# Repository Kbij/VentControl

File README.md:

# VentControl

Firmware for a custom made RP-2040 board with relays. Used for Ventilation control.

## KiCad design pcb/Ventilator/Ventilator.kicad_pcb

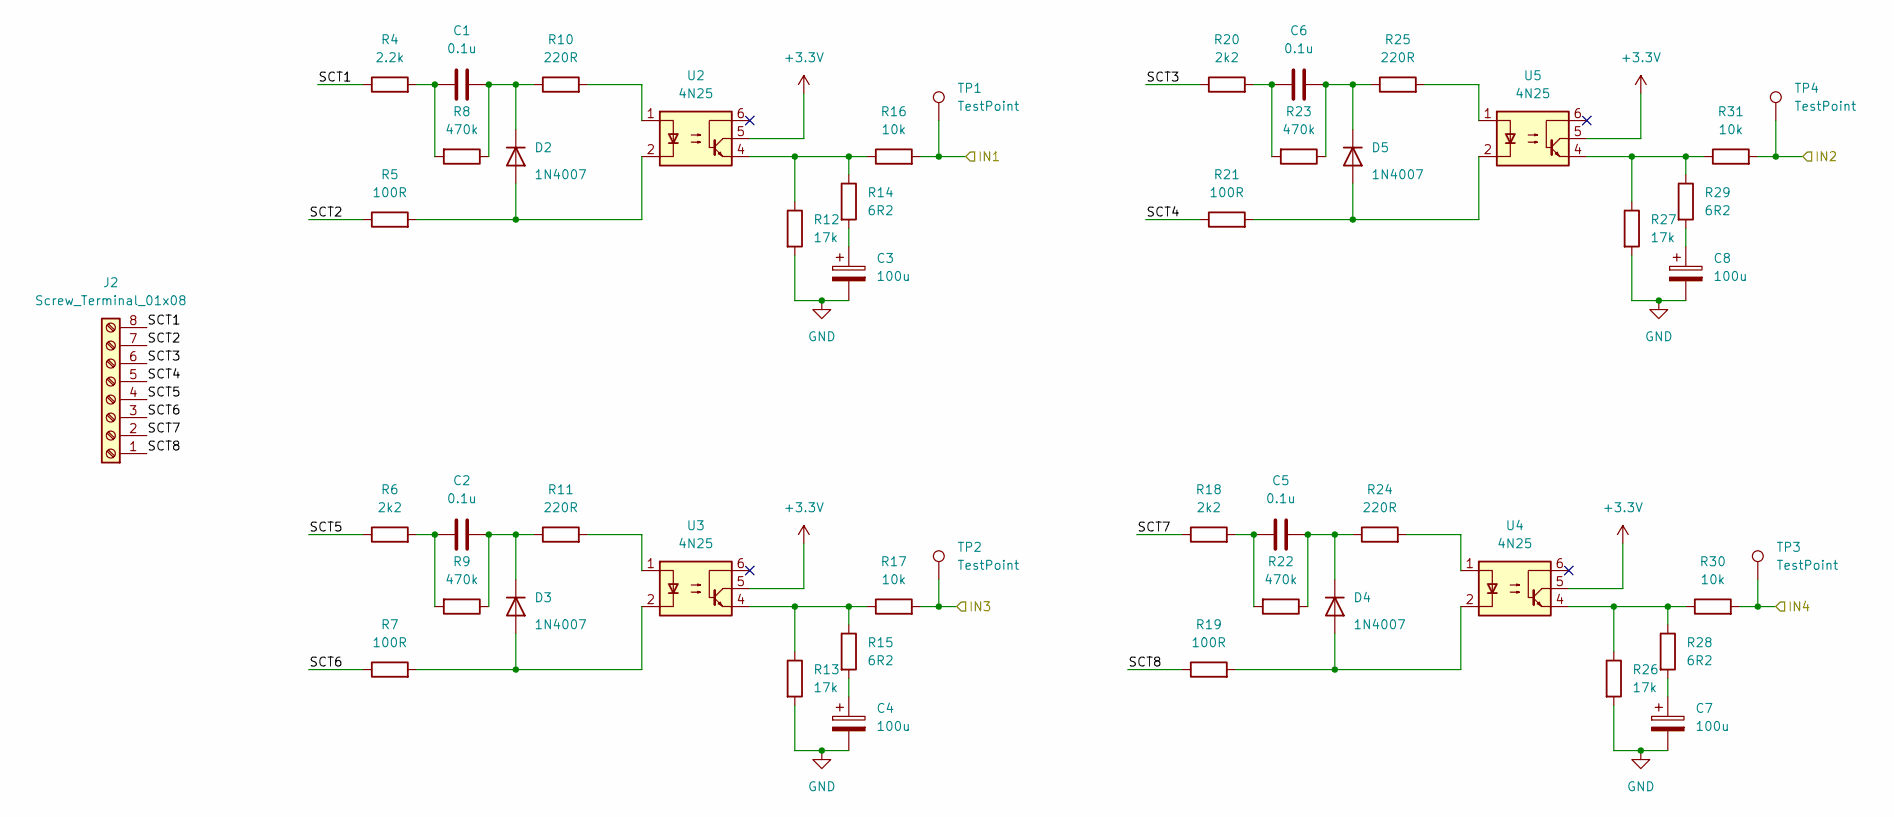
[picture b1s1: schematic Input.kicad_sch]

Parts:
C1, C2, C5, C6: 0.1u; C_Rect_L18.0mm_W5.0mm_P15.00mm_FKS3_FKP3
C3, C4, C7, C8: 100u; C_1206_3216Metric_Pad1.33x1.80mm_HandSolder
D2, D3, D4, D5: 1N4007; D_DO-41_SOD81_P10.16mm_Horizontal
J2: Screw_Terminal_01x08; TerminalBlock_Phoenix_MKDS-1,5-8_1x08_P5.00mm_Horizontal
R4: 2.2k; R_2512_6332Metric
R5, R7, R19, R21: 100R; R_0805_2012Metric_Pad1.20x1.40mm_HandSolder
R6, R18, R20: 2k2; R_2512_6332Metric
R8, R9, R22, R23: 470k; R_2512_6332Metric
R10, R11, R24, R25: 220R; R_0805_2012Metric_Pad1.20x1.40mm_HandSolder
R12, R13, R26, R27: 17k; R_0805_2012Metric_Pad1.20x1.40mm_HandSolder
R14, R15, R28, R29: 6R2; R_0805_2012Metric_Pad1.20x1.40mm_HandSolder
R16, R17, R30, R31: 10k; R_0805_2012Metric_Pad1.20x1.40mm_HandSolder
TP1, TP2, TP3, TP4: TestPoint; TestPoint_Bridge_Pitch2.54mm_Drill1.0mm
U2, U3, U4, U5: 4N25; DIP-6_W7.62mm

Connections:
+3.3V: U2.5, U3.5, U4.5, U5.5; also elsewhere on the board
/CPU/IN1: R16.2, TP1.1; also elsewhere on the board
/CPU/IN2: R31.2, TP4.1; also elsewhere on the board
/CPU/IN3: R17.2, TP2.1; also elsewhere on the board
/CPU/IN4: R30.2, TP3.1; also elsewhere on the board
/Input/SCT1: J2.8, R4.1; also elsewhere on the board
/Input/SCT2: J2.7, R5.1; also elsewhere on the board
/Input/SCT3: J2.6, R20.1; also elsewhere on the board
/Input/SCT4: J2.5, R21.1; also elsewhere on the board
/Input/SCT5: J2.4, R6.1; also elsewhere on the board
/Input/SCT6: J2.3, R7.1; also elsewhere on the board
/Input/SCT7: J2.2, R18.1; also elsewhere on the board
/Input/SCT8: J2.1, R19.1; also elsewhere on the board
GND: C3.2, C4.2, C7.2, C8.2, R12.2, R13.2, R26.2, R27.2; also elsewhere on the board
unnamed 30: C1.1, D2.1 (K), R8.1, R10.1; also elsewhere on the board
unnamed 31: C1.2, R4.2, R8.2; also elsewhere on the board
unnamed: C2.1, D3.1 (K), R9.1, R11.1
unnamed: C2.2, R6.2, R9.2
unnamed: C3.1, R14.2
unnamed: C4.1, R15.2
unnamed: C5.1, D4.1 (K), R22.1, R24.1
unnamed: C5.2, R18.2, R22.2
unnamed: C6.1, D5.1 (K), R23.1, R25.1
unnamed: C6.2, R20.2, R23.2
unnamed: C7.1, R28.2
unnamed: C8.1, R29.2
unnamed: D2.2 (A), R5.2, U2.2
unnamed: D3.2 (A), R7.2, U3.2
unnamed: D4.2 (A), R19.2, U4.2
unnamed: D5.2 (A), R21.2, U5.2
unnamed: R10.2, U2.1
unnamed: R11.2, U3.1
unnamed: R12.1, R14.1, R16.1, U2.4
unnamed: R13.1, R15.1, R17.1, U3.4
unnamed: R24.2, U4.1
unnamed: R25.2, U5.1
unnamed: R26.1, R28.1, R30.1, U4.4
unnamed: R27.1, R29.1, R31.1, U5.4

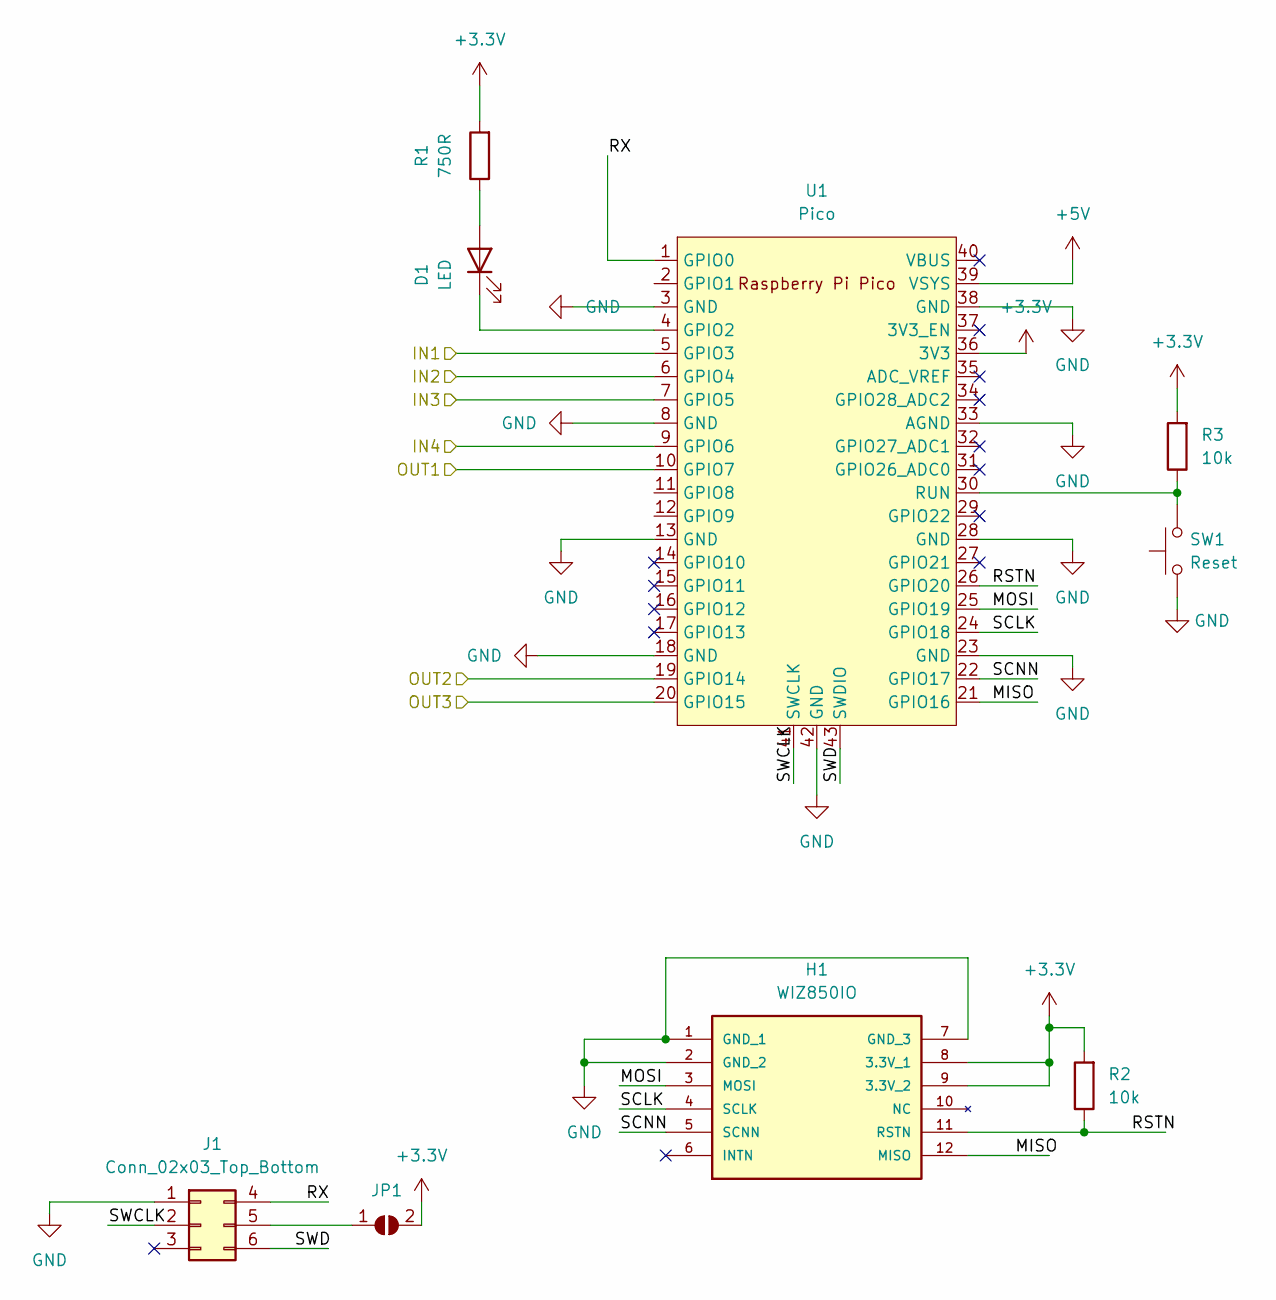
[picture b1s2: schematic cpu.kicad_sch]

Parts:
D1: LED; LED_D3.0mm
H1: WIZ850IO; MANUFACTURER_PART_NUMBER WIZ850IO
J1: Conn_02x03_Top_Bottom; PinHeader_2x03_P2.54mm_Vertical
JP1: SolderJumper_2_Open
R1: 750R; R_0805_2012Metric_Pad1.20x1.40mm_HandSolder
R2, R3: 10k; R_0805_2012Metric
SW1: Reset; SW_SPST_EVPBF
U1: Pico; RPi_Pico_SMD_TH

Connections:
+3.3V: H1.8 (3.3V_1), H1.9 (3.3V_2), JP1.2 (B), R1.2, R2.2, R3.2, U1.36 (3V3); also elsewhere on the board
+5V: U1.39 (VSYS); also elsewhere on the board
/CPU/IN1: U1.5 (GPIO3); also elsewhere on the board
/CPU/IN2: U1.6 (GPIO4); also elsewhere on the board
/CPU/IN3: U1.7 (GPIO5); also elsewhere on the board
/CPU/IN4: U1.9 (GPIO6); also elsewhere on the board
/CPU/MISO: H1.12 (MISO), U1.21 (GPIO16)
/CPU/MOSI: H1.3 (MOSI), U1.25 (GPIO19)
/CPU/OUT1: U1.10 (GPIO7); also elsewhere on the board
/CPU/OUT2: U1.19 (GPIO14); also elsewhere on the board
/CPU/OUT3: U1.20 (GPIO15); also elsewhere on the board
/CPU/RSTN: H1.11 (RSTN), R2.1, U1.26 (GPIO20)
/CPU/RX: J1.4, U1.1 (GPIO0)
/CPU/SCLK: H1.4 (SCLK), U1.24 (GPIO18)
/CPU/SCNN: H1.5 (SCNN), U1.22 (GPIO17)
/CPU/SWCLK: J1.2, U1.41 (SWCLK)
/CPU/SWD: J1.6, U1.43 (SWDIO)
GND: H1.1 (GND_1), H1.2 (GND_2), H1.7 (GND_3), J1.1, SW1.1, U1.3 (GND), U1.8 (GND), U1.13 (GND), U1.18 (GND), U1.23 (GND), U1.28 (GND), U1.33 (AGND), U1.38 (GND), U1.42 (GND); also elsewhere on the board
unnamed: D1.1 (K), U1.4 (GPIO2)
unnamed: D1.2 (A), R1.1
unnamed: J1.5, JP1.1 (A)
unnamed: R3.1, SW1.2, U1.30 (RUN)

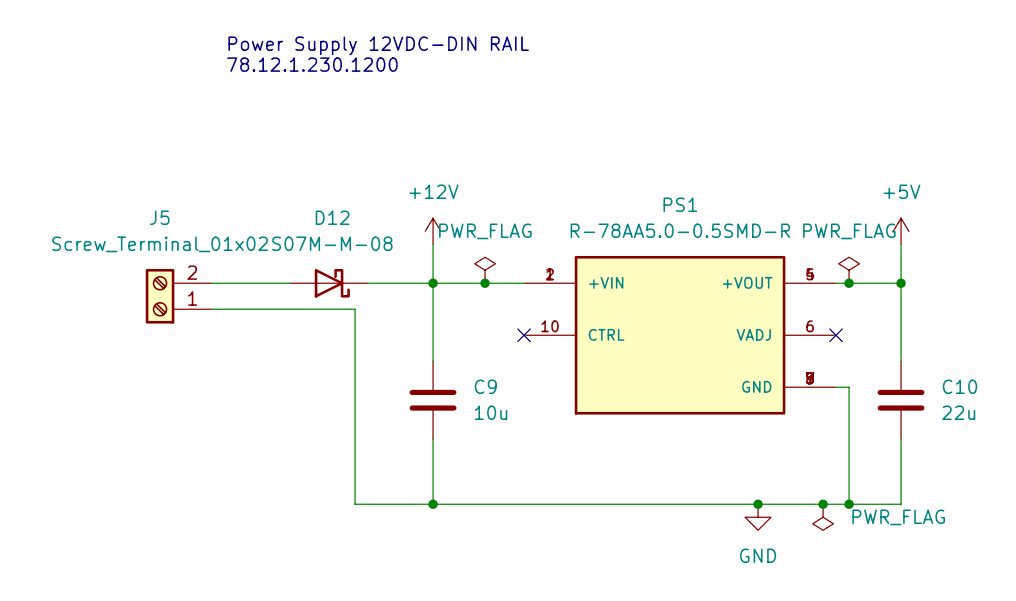
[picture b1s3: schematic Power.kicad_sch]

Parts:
C9: 10u; C_0805_2012Metric_Pad1.18x1.45mm_HandSolder
C10: 22u; C_0805_2012Metric_Pad1.18x1.45mm_HandSolder
D12: S07M-M-08; D_SMF
J5: Screw_Terminal_01x02; TerminalBlock_bornier-2_P5.08mm
PS1: R-78AA5.0-0.5SMD-R; CONV_R-78AA3.3-1.0SMD; PARTREV 5/2019

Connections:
+5V: C10.1, PS1.4 (+VOUT), PS1.5 (+VOUT); also elsewhere on the board
+12V: C9.1, D12.1 (K), PS1.1 (+VIN), PS1.2 (+VIN); also elsewhere on the board
GND: C9.2, C10.2, J5.1, PS1.3 (GND), PS1.7 (GND), PS1.8 (GND), PS1.9 (GND); also elsewhere on the board
unnamed: D12.2 (A), J5.2

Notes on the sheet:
Power Supply 12VDC-DIN RAIL 78.12.1.230.1200

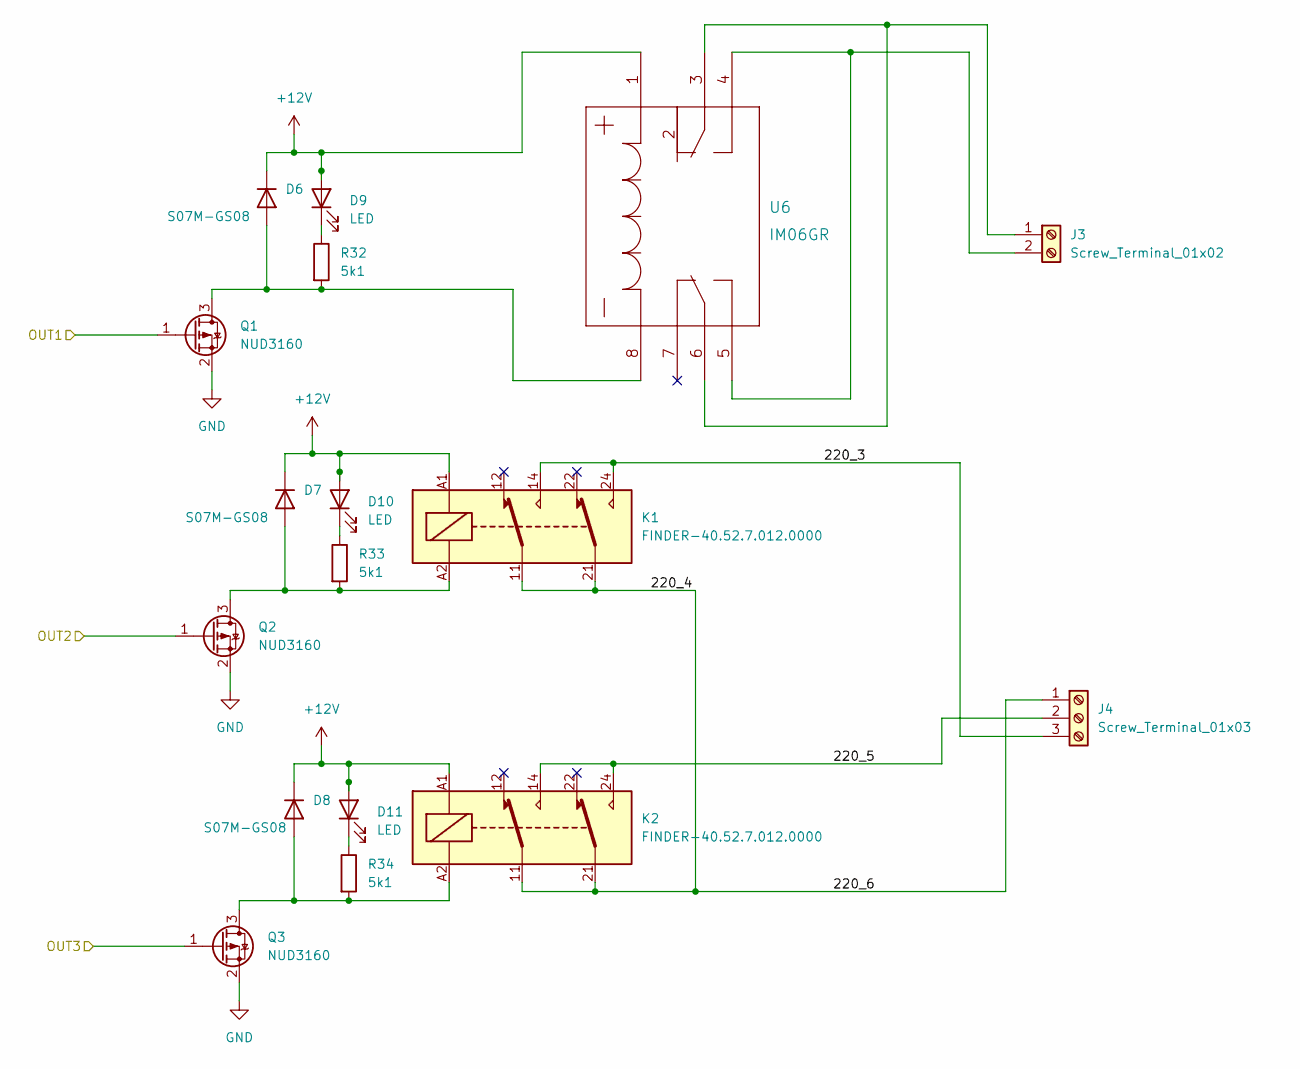
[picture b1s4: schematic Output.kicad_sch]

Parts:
D6, D7, D8: S07M-GS08; D_SMF
D9, D10, D11: LED; LED_D3.0mm
J3: Screw_Terminal_01x02; TerminalBlock_Phoenix_MKDS-1,5-2-5.08_1x02_P5.08mm_Horizont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
J4: Screw_Terminal_01x03; TerminalBlock_Phoenix_MKDS-1,5-3-5.08_1x03_P5.08mm_Horizont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
K1, K2: FINDER-40.52.7.012.0000; Relay_DPDT_Finder_40.52
Q1, Q2, Q3: NUD3160; SOT-23
R32, R33, R34: 5k1; R_0805_2012Metric_Pad1.20x1.40mm_HandSolder
U6: IM06GR

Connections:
+12V: D6.1 (K), D7.1 (K), D8.1 (K), D9.2 (A), D10.2 (A), D11.2 (A), K1.A1, K2.A1, U6.1; also elsewhere on the board
/CPU/OUT1: Q1.1 (G); also elsewhere on the board
/CPU/OUT2: Q2.1 (G); also elsewhere on the board
/CPU/OUT3: Q3.1 (G); also elsewhere on the board
/Output/220_3: J4.3, K1.14, K1.24
/Output/220_4: J4.1, K1.11, K1.21, K2.11, K2.21; also elsewhere on the board
/Output/220_5: J4.2, K2.14, K2.24; also elsewhere on the board
GND: Q1.2 (S), Q2.2 (S), Q3.2 (S); also elsewhere on the board
unnamed: D6.2 (A), Q1.3 (D), R32.2, U6.8
unnamed: D7.2 (A), K1.A2, Q2.3 (D), R33.2
unnamed 50: D8.2 (A), K2.A2, Q3.3 (D), R34.2; also elsewhere on the board
unnamed: D9.1 (K), R32.1
unnamed: D10.1 (K), R33.1
unnamed 53: D11.1 (K), R34.1; also elsewhere on the board
unnamed: J3.1, U6.3, U6.6
unnamed: J3.2, U6.4, U6.5

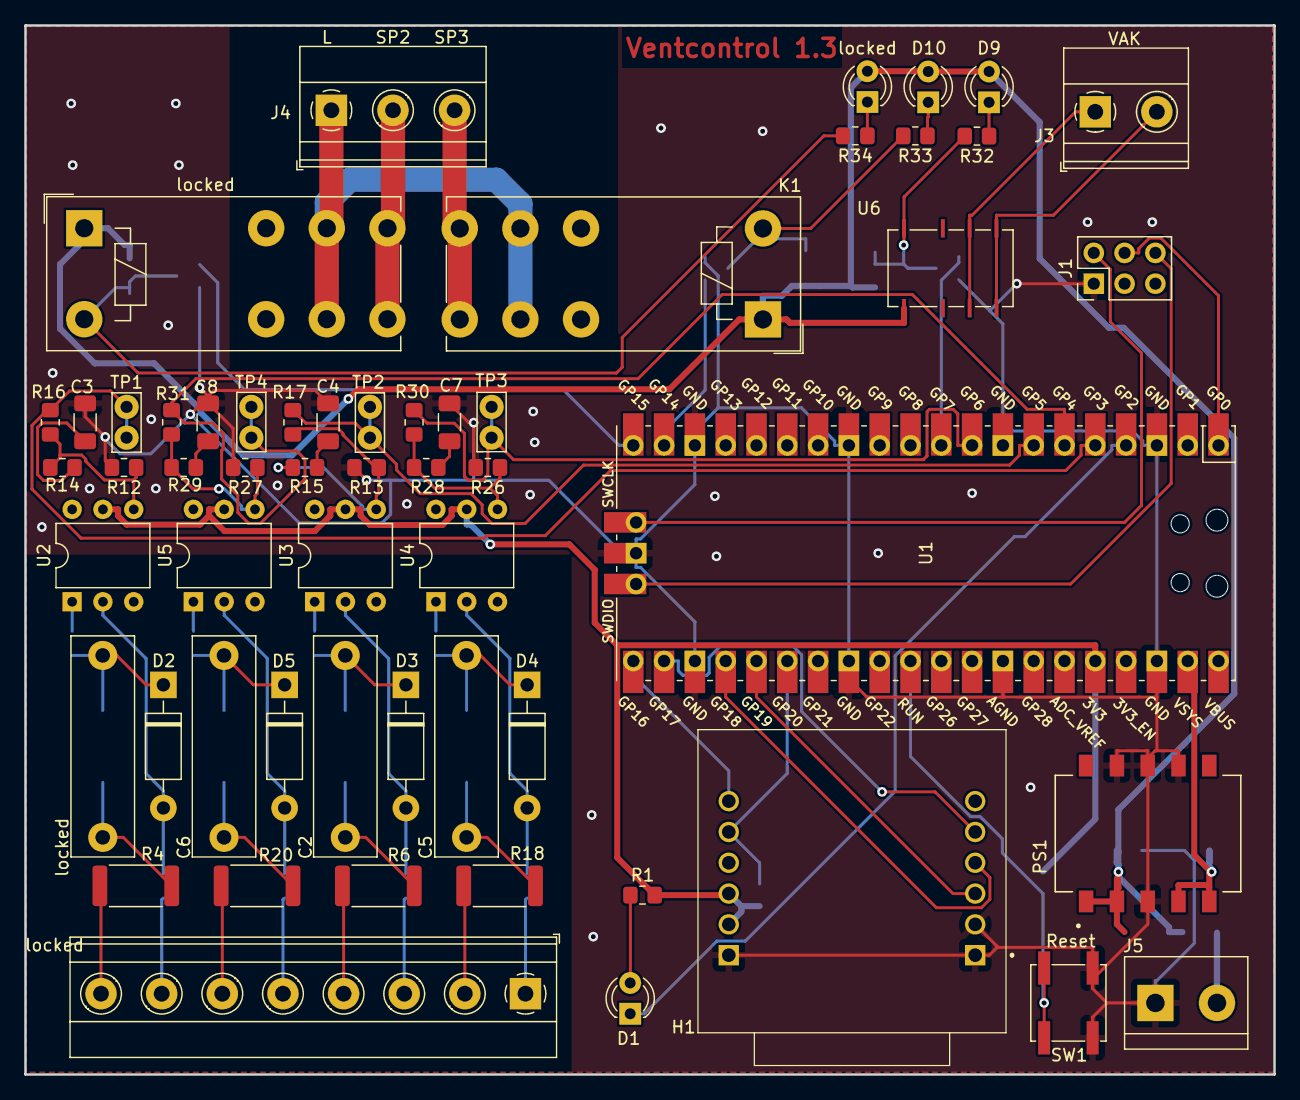
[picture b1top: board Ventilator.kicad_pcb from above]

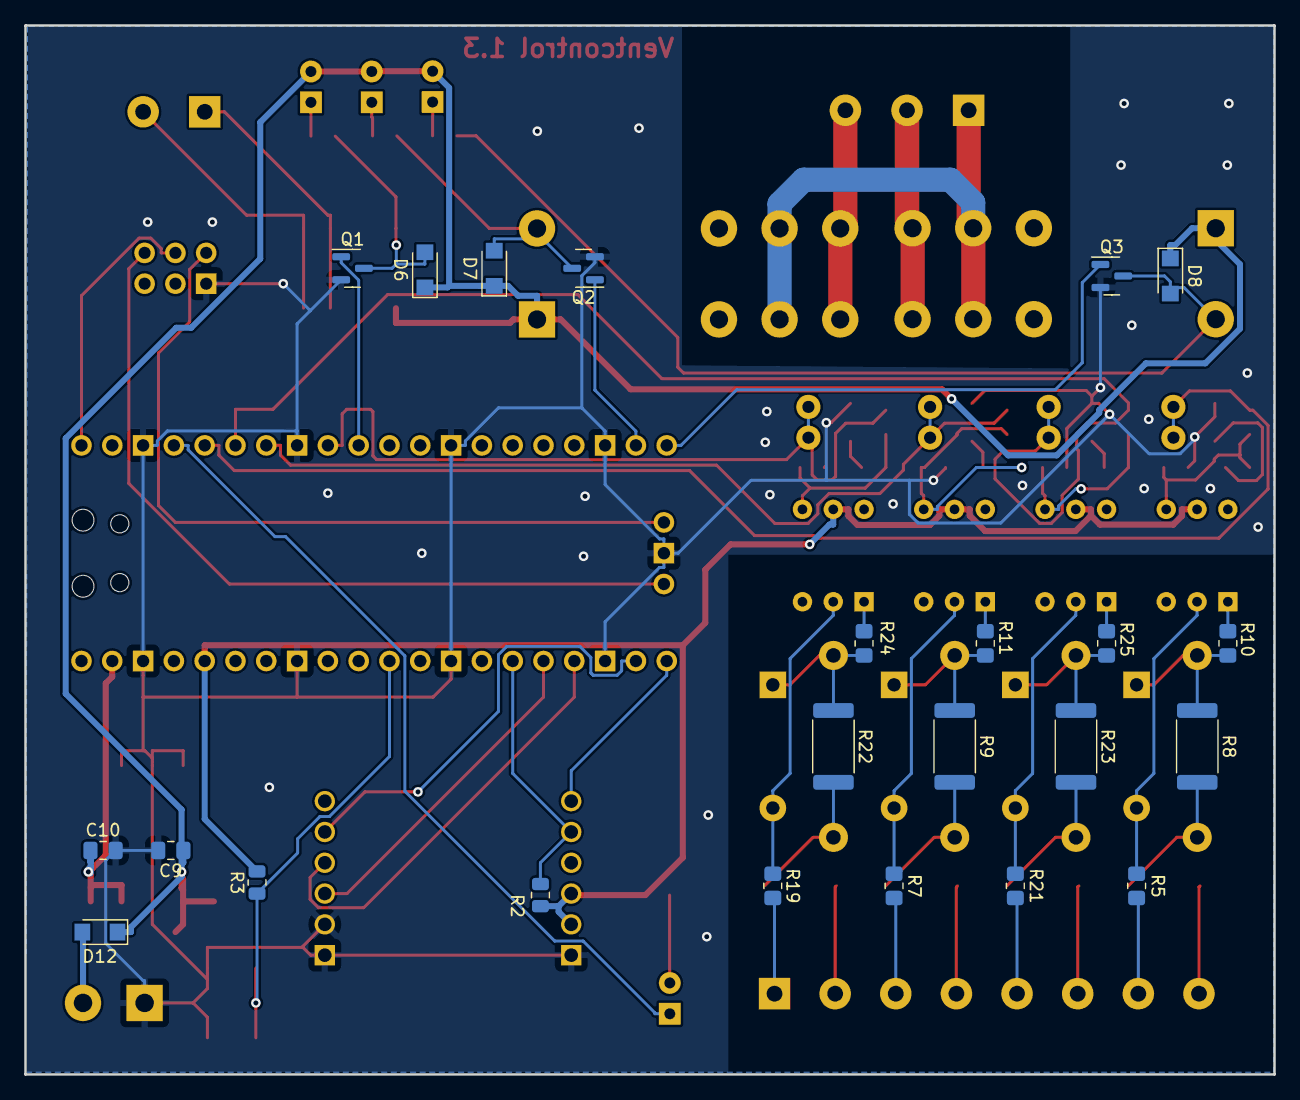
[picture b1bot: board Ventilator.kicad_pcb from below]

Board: 2 copper layers, 103.0 x 86.5 mm, 79 parts (23 on the bottom side), 66 nets.

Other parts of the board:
locked: Screw_Terminal_01x08; TerminalBlock_Phoenix_MKDS-1,5-8_1x08_P5.00mm_Horizontal
locked#2: FINDER-40.52.7.012.0000; Relay_DPDT_Finder_40.52
locked#3: LED; LED_D3.0mm
locked#4: 0.1u; C_Rect_L18.0mm_W5.0mm_P15.00mm_FKS3_FKP3

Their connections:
+12V: locked#2.A1, locked#3.2 (A); also elsewhere on the board
/Input/SCT1: locked.8; also elsewhere on the board
/Input/SCT2: locked.7; also elsewhere on the board
/Input/SCT3: locked.6; also elsewhere on the board
/Input/SCT4: locked.5; also elsewhere on the board
/Input/SCT5: locked.4; also elsewhere on the board
/Input/SCT6: locked.3; also elsewhere on the board
/Input/SCT7: locked.2; also elsewhere on the board
/Input/SCT8: locked.1; also elsewhere on the board
/Output/220_4: locked#2.11, locked#2.21; also elsewhere on the board
/Output/220_5: locked#2.14, locked#2.24; also elsewhere on the board
unnamed 30: locked#4.1; also elsewhere on the board
unnamed 31: locked#4.2; also elsewhere on the board
unnamed 50: locked#2.A2; also elsewhere on the board
unnamed 53: locked#3.1 (K); also elsewhere on the board

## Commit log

2022-09-11 - initial files
2022-09-20 - TCP Server working
2022-09-20 - Send/Receive works. needs cleanup, but is working ...
2022-09-25 - messages working
2022-09-26 - with blink
2022-09-28 - close connection on timeout
2022-10-02 -pcb
2022-10-03 -components placed
2022-10-04 - as send to JCLPCB
2022-10-04 - add heartbeat
2022-10-22 - resister values
2022-12-26 - added rp2040, multiple sheets, etc...
2022-12-28 - all parts connected, placed partially
2022-12-30 - voor omschakeling naar rp pico
2022-12-30 - voor autorouter
2022-12-30 - as ordered (30/12/2022)
2023-01-11 - copied code from test project
2023-01-11 - missing files
2023-01-11 - remove old implementation
2023-01-11 - remove obsolete
2023-01-14 -relais working. close socket has issue
2023-01-14 - fix hang on close
2023-01-15 - handle inputs
2023-01-15 - inputs working
2023-01-16 - boost working
2023-01-16 - sending boost value to app
2023-01-19 -cleanup ventcontrol.c (has bug)
2023-01-19 - fix issue with duplicate ventcontrol task
2023-01-20 - changed timings
2023-01-29 - fix hang ?
2023-01-30 - Firmware test tool
2023-01-30 -Ventcontrol 1.2 (routed)
2023-01-31 - last changes
2023-01-31 - gitignore
2023-02-18 - small change in gnd plane
2023-04-06 - as ordered

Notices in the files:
parts and their libraries:
Copyright 2021 Accelerated Designs. All rights reserved.
